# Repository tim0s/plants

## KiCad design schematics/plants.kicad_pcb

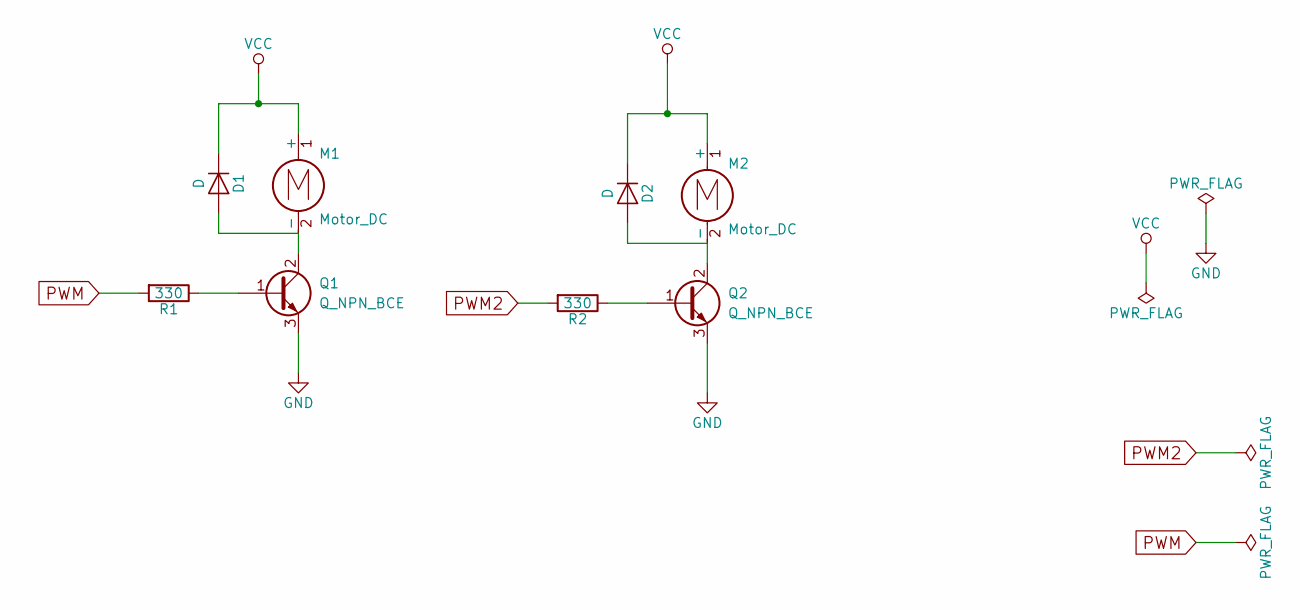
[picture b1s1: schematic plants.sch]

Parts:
D1, D2: D; D_DO-27_P12.70mm_Horizontal
M1, M2: Motor_DC; TerminalBlock_Pheonix_PT-3.5mm_2pol
Q1, Q2: Q_NPN_BCE; TO-126_Vertical
R1, R2: 330; R_Axial_DIN0204_L3.6mm_D1.6mm_P7.62mm_Horizontal

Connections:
GND: Q1.3 (E), Q2.3 (E)
unnamed: D1.2 (A), M1.2 (-), Q1.2 (C)
unnamed: D2.2 (A), M2.2 (-), Q2.2 (C)
unnamed: Q1.1 (B), R1.1
unnamed: Q2.1 (B), R2.1
PWM: R1.2
PWM2: R2.2
VCC: D1.1 (K), D2.1 (K), M1.1 (+), M2.1 (+)

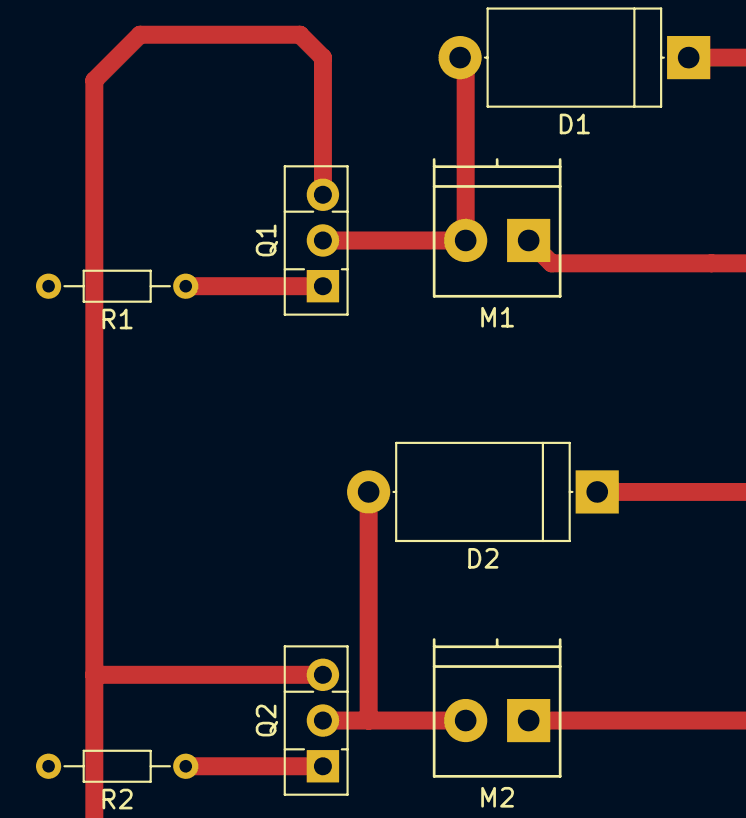
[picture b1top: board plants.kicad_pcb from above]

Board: 2 copper layers, 8 parts (0 on the bottom side), 6 nets.

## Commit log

2018-03-01 move to templates and db backend, add pi emulation
2018-03-05 small redesign, added holder for power supply pcb
2018-03-07 added temp sensor
2018-03-29 automatically decide if we should use emulation or not
2018-03-29 seperate template for headerbox
2018-03-29 start working on graph viewer
2018-04-01 control fans
2018-04-01 only store temp if it is different than last one
2018-05-17 add dishwasher wheel
